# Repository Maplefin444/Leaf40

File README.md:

# Leaf40
This is my custom split spacebar 40% keyboard, with a custom PCB, and a 3D printed case.

***This is a work in progress, this repository houses all files pertaining to the project.***

## Parts List
- [ ] PCB
- [ ] Case
- [ ] Plate
- [ ] Keycaps
- [ ] MX-Style Switches
- [ ] SOD-123 diodes (44 total)
- [ ] Arduino Pro Micro
- [ ] Screw-in Stabilizers (2x2u)

## Layout
The layout can be found in the `Keyboard Layout` directory.

Layer 0 is the default layer, while each layer will have the corresponding layer switch keys darkened.

As of right now, non-zero layers are a ***work in progress and will change.***

## PCB
The PCB was designed on KiCad and can be found in the `PCB` directory.

MarbastLib is required to have the MX switch footprints.

## Firmware

This keyboard supports QMK and Vial. Both files can be found in the `Firmware` directory, `default` for regular QMK, and `vial` for the Vial firmware.

These firmwares can be flashed using the QMK Toolbox. 

The QMK firmware has ASCII art for the keyboard layouts, for ease of editing.

### Flashing QMK Firmware
Add the `default` keymap, info JSON, and rules file into a directory named `leaf40` under `keyboards` in your QMK directory. Then, compile using `qmk compile -kb leaf40 -km default`. Flash using QMK Toolbox.

### Flashing Vial Firmware
Add the `vial` keymap, info JSON, and rules file into a directory named `leaf40` under `keyboards` in your Vial directory. Then, compile using `make leaf40:vial` in your `vial-qmk` directory. Flash using QMK Toolbox.

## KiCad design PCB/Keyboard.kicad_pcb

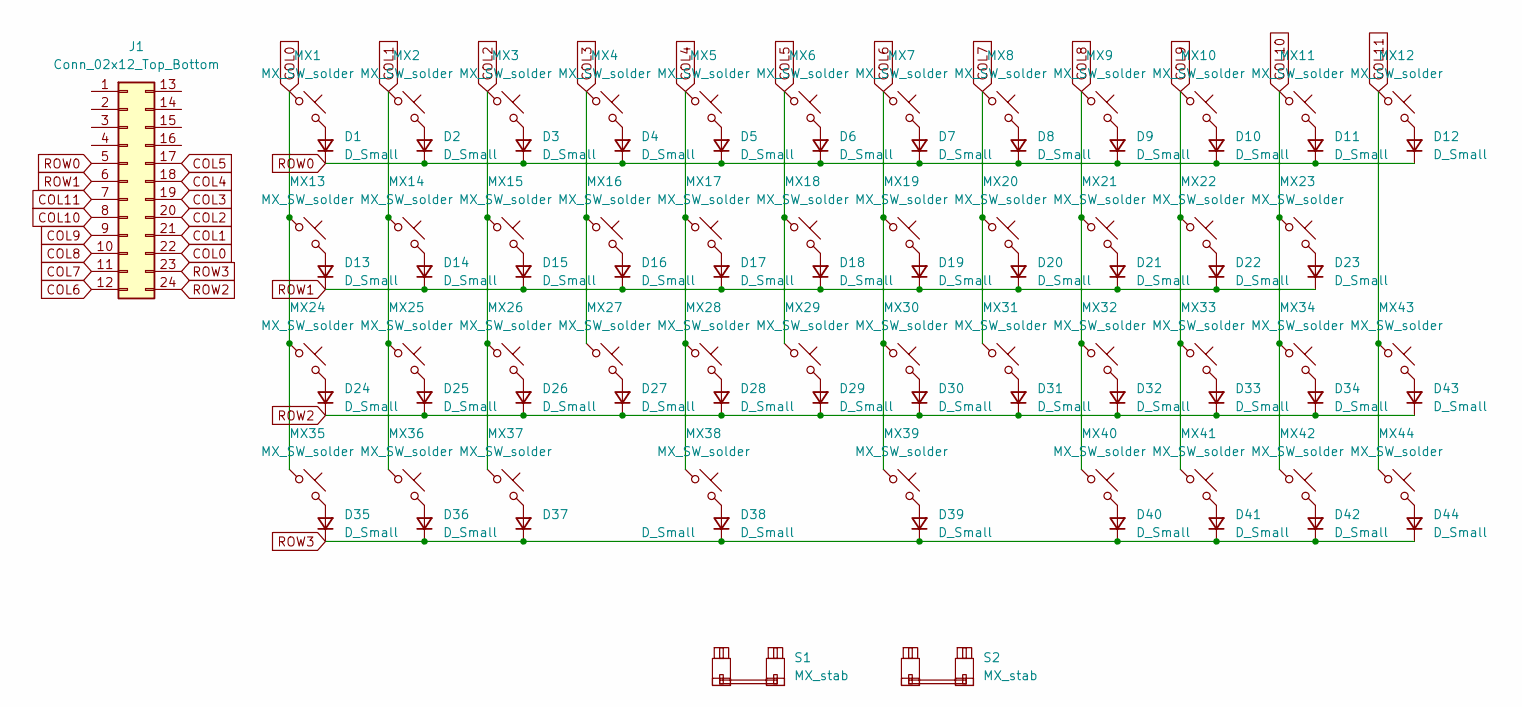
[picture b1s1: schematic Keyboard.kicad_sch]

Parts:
D1, D2, D3, D4, D5, D6, D7, D8, D9, D10, D11, D12, D13, D14, D15, D16, D17, D18, D19, D20, D21, D22, D23, D24, D25, D26, D27, D28, D29, D30, D31, D32, D33, D34, D35, D36, D37, D38, D39, D40, D41, D42, D43, D44: D_Small; D_SOD-123
J1: Conn_02x12_Top_Bottom; ProMicro_Reversible_Single
MX1, MX2, MX3, MX4, MX5, MX6, MX7, MX8, MX9, MX10, MX11, MX12, MX14, MX15, MX16, MX17, MX18, MX19, MX20, MX21, MX22, MX25, MX26, MX27, MX28, MX29, MX30, MX31, MX32, MX33, MX36, MX38, MX39, MX41, MX43, MX44: MX_SW_solder; SW_MX_1u
MX13, MX34, MX35, MX37, MX40, MX42: MX_SW_solder; SW_MX_1.25u
MX23, MX24: MX_SW_solder; SW_MX_1.75u
S1: MX_stab; STAB_MX_2.25u
S2: MX_stab; STAB_MX_2.75u

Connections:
COL0: J1.22, MX1.1, MX13.1, MX24.1, MX35.1
COL1: J1.21, MX2.1, MX14.1, MX25.1, MX36.1
COL2: J1.20, MX3.1, MX15.1, MX26.1, MX37.1
COL3: J1.19, MX4.1, MX16.1, MX27.1
COL4: J1.18, MX5.1, MX17.1, MX28.1, MX38.1
COL5: J1.17, MX6.1, MX18.1, MX29.1
COL6: J1.12, MX7.1, MX19.1, MX30.1, MX39.1
COL7: J1.11, MX8.1, MX20.1, MX31.1
COL8: J1.10, MX9.1, MX21.1, MX32.1, MX40.1
COL9: J1.9, MX10.1, MX22.1, MX33.1, MX41.1
COL10: J1.8, MX11.1, MX23.1, MX34.1, MX42.1
COL11: J1.7, MX12.1, MX43.1, MX44.1
unnamed: D1.2 (A), MX1.2
unnamed: D2.2 (A), MX2.2
unnamed: D3.2 (A), MX3.2
unnamed: D4.2 (A), MX4.2
unnamed: D5.2 (A), MX5.2
unnamed: D6.2 (A), MX6.2
unnamed: D7.2 (A), MX7.2
unnamed: D8.2 (A), MX8.2
unnamed: D9.2 (A), MX9.2
unnamed: D10.2 (A), MX10.2
unnamed: D11.2 (A), MX11.2
unnamed: D12.2 (A), MX12.2
unnamed: D13.2 (A), MX13.2
unnamed: D14.2 (A), MX14.2
unnamed: D15.2 (A), MX15.2
unnamed: D16.2 (A), MX16.2
unnamed: D17.2 (A), MX17.2
unnamed: D18.2 (A), MX18.2
unnamed: D19.2 (A), MX19.2
unnamed: D20.2 (A), MX20.2
unnamed: D21.2 (A), MX21.2
unnamed: D22.2 (A), MX22.2
unnamed: D23.2 (A), MX23.2
unnamed: D24.2 (A), MX24.2
unnamed: D25.2 (A), MX25.2
unnamed: D26.2 (A), MX26.2
unnamed: D27.2 (A), MX27.2
unnamed: D28.2 (A), MX28.2
unnamed: D29.2 (A), MX29.2
unnamed: D30.2 (A), MX30.2
unnamed: D31.2 (A), MX31.2
unnamed: D32.2 (A), MX32.2
unnamed: D33.2 (A), MX33.2
unnamed: D34.2 (A), MX34.2
unnamed: D35.2 (A), MX35.2
unnamed: D36.2 (A), MX36.2
unnamed: D37.2 (A), MX37.2
unnamed: D38.2 (A), MX38.2
unnamed: D39.2 (A), MX39.2
unnamed: D40.2 (A), MX40.2
unnamed: D41.2 (A), MX41.2
unnamed: D42.2 (A), MX42.2
unnamed: D43.2 (A), MX43.2
unnamed: D44.2 (A), MX44.2
ROW0: D1.1 (K), D2.1 (K), D3.1 (K), D4.1 (K), D5.1 (K), D6.1 (K), D7.1 (K), D8.1 (K), D9.1 (K), D10.1 (K), D11.1 (K), D12.1 (K), J1.5
ROW1: D13.1 (K), D14.1 (K), D15.1 (K), D16.1 (K), D17.1 (K), D18.1 (K), D19.1 (K), D20.1 (K), D21.1 (K), D22.1 (K), D23.1 (K), J1.6
ROW2: D24.1 (K), D25.1 (K), D26.1 (K), D27.1 (K), D28.1 (K), D29.1 (K), D30.1 (K), D31.1 (K), D32.1 (K), D33.1 (K), D34.1 (K), D43.1 (K), J1.24
ROW3: D35.1 (K), D36.1 (K), D37.1 (K), D38.1 (K), D39.1 (K), D40.1 (K), D41.1 (K), D42.1 (K), D44.1 (K), J1.23

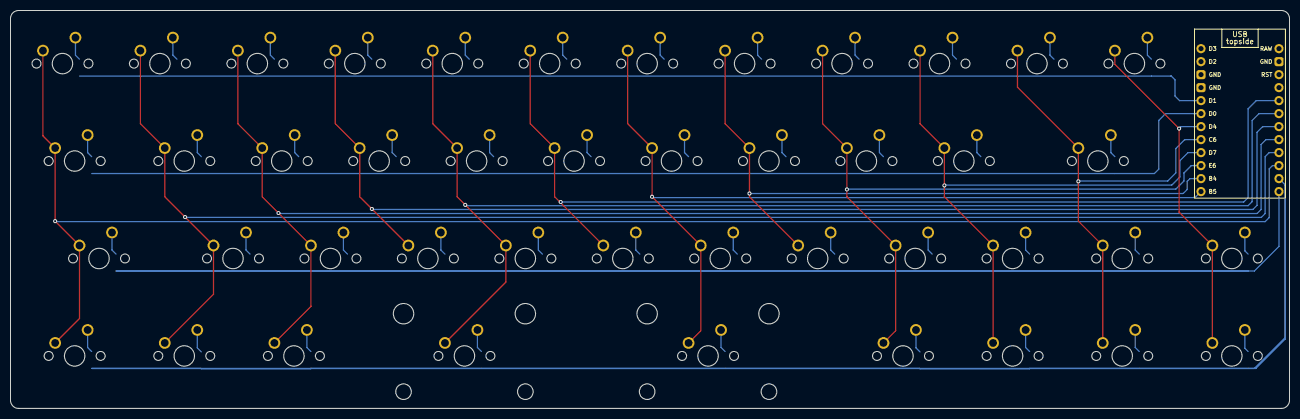
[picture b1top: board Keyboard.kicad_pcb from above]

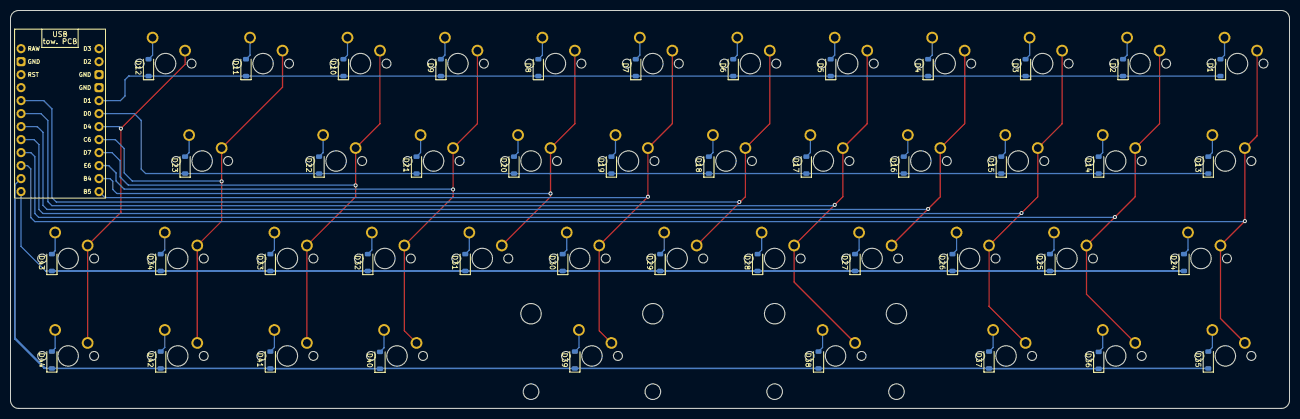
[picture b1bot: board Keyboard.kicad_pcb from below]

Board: 2 copper layers, 250.0 x 77.8 mm, 91 parts (44 on the bottom side), 60 nets.

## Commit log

2023-08-03 Add PCB and layers
2023-08-13 Upload firmware files
2023-08-13 Add documentation for firmware
2023-08-13 Add second layer switch
2023-08-13 Fix firmware error
2023-08-16 Fix Vial JSON
